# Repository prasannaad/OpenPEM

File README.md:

# OpenPEM
Open-Source Personal Exposure Monitor - PM2.5

# What is OpenPEM? 
OpenPEM is an Open-Source hardware for continuous monitoring of personal expsoure to PM2.5. The hardware includes a MCU board and a PM sensor from sensirion. We have used an SPS30 which is basically an Optical Particle Counter. OpenPEM sends alerts to the users via BLE when tbe expsoure levels exceeds. 

# Why OpenPEM? 

Exposure to fine particles can also affect lung function and worsen medical conditions such as asthma and heart disease. Scientific studies have linked increases in daily PM2.5 exposure with increased respiratory and cardiovascular hospital admissions, emergency department visits and deaths. Studies also suggest that long term exposure to fine particulate matter may be associated with increased rates of chronic bronchitis, reduced lung function and increased mortality from lung cancer and heart disease. People with breathing and heart problems, children and the elderly may be particularly sensitive to PM2.5.

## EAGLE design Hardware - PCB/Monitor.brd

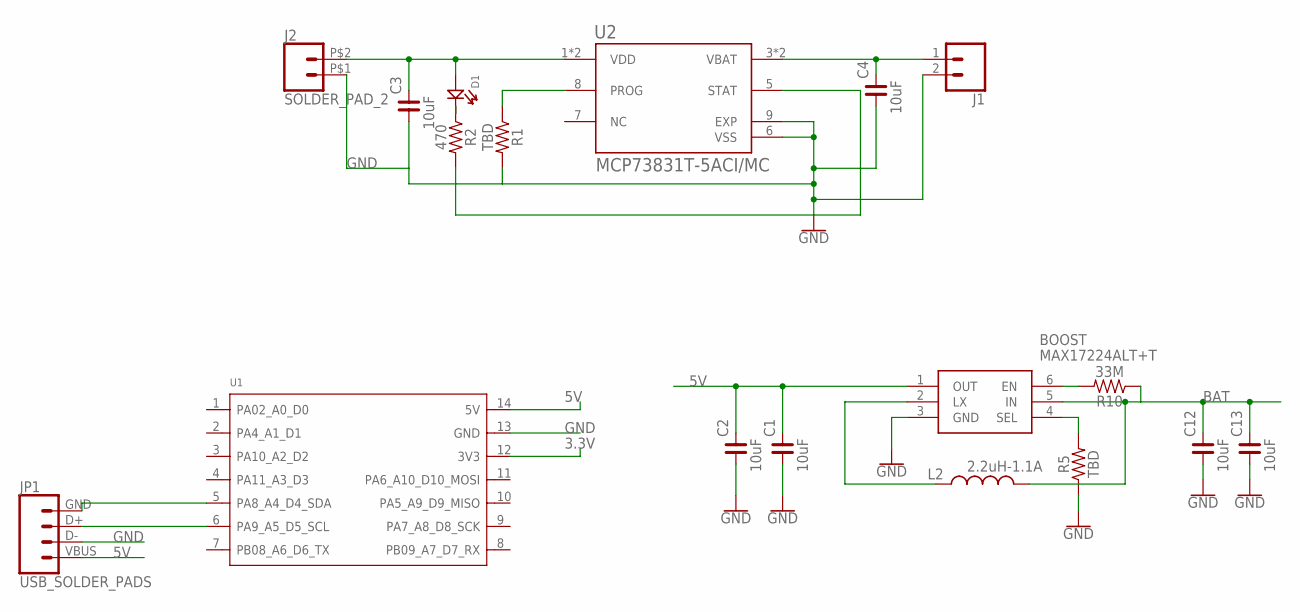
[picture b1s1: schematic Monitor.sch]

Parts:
BOOST: MAX17224ALT+T; MAX17220ALT
C1, C2, C3, C4, C12, C13: 10uF; C0805
D1: LED0603; LED-0603
J1: CONN_021X02_NO_SILK; 1X02_NO_SILK
J2: SOLDER_PAD_2
JP1: USB_SOLDER_PADS; USB-SOLDER-PADS
L2: 2.2uH-1.1A; LPS4012; MPN SRN2009T-100M
R1, R5: TBD; 0603
R2: 470; 0603
R10: 33M; 0603
U1: MOUDLE-SEEEDUINO-XIAO; MOUDLE14P-2.54-21X17.8MM
U2: MCP73831T-5ACI/MC; SON50P200X300X100-9N

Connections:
3.3V: U1.12 (3V3)
5V: BOOST.1 (OUT), C1.2, C2.2, JP1.VBUS (1), U1.14 (5V)
BAT: BOOST.5 (IN), C12.2, C13.2, L2.2, R10.1
GND: BOOST.3 (GND), C1.1, C2.1, C3.1, C4.1, C12.1, C13.1, J1.2, J2.P$1 (1), JP1.D- (2), R1.2, R5.1, U1.13 (GND), U2.6 (VSS), U2.9 (EXP)
unnamed: JP1.GND (4), U1.5 (PA8_A4_D4_SDA)
unnamed: JP1.D+ (3), U1.6 (PA9_A5_D5_SCL)
unnamed: C4.2, J1.1, U2.3 (VBAT), U2.4 (VBAT)
unnamed: R1.1, U2.8 (PROG)
unnamed: C3.2, D1.+, J2.P$2 (2), U2.1 (VDD), U2.2 (VDD)
unnamed: D1.-, R2.1
unnamed: R2.2, U2.5 (STAT)
unnamed: BOOST.6 (EN), R10.2
unnamed: BOOST.2 (LX), L2.1
unnamed: BOOST.4 (SEL), R5.2

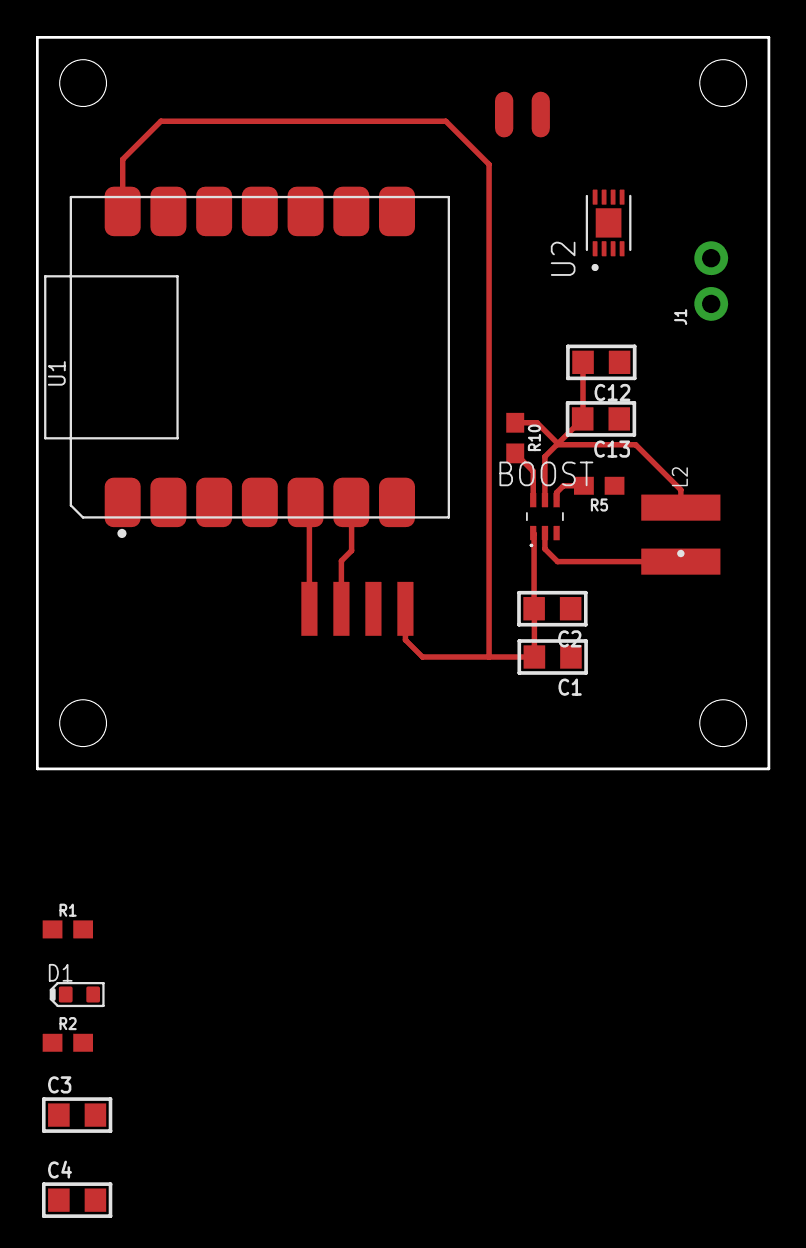
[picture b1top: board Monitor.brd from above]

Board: 2 copper layers, 40.6 x 40.6 mm, 18 parts (0 on the bottom side), 13 nets.

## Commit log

2022-11-11 Create Hardware - PCB
2022-11-11 Create LICENSE

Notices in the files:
parts and their libraries:
SparkFun-Resistors: Licensing: Creative Commons ShareAlike 4.0 International - https://creativecommons.org/licenses/by-sa/4.0
rc-master-smd: Copyright (C) 2007, Bob Starr
